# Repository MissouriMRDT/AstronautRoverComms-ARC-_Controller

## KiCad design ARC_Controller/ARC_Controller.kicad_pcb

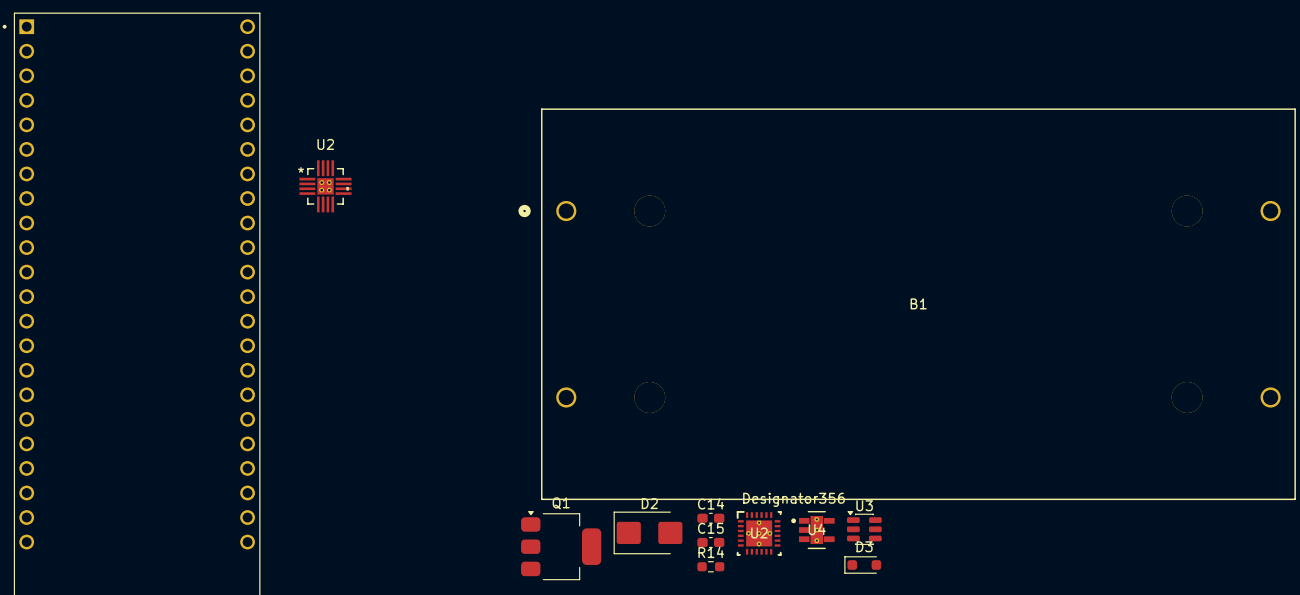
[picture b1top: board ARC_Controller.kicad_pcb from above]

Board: 2 copper layers, 12 parts (0 on the bottom side), 8 nets, no tracks yet.

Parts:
B1: BK-18650-PC4; BK-18650-PC4_MPD
C14: 0.1uF; C_0603_1608Metric_Pad1.08x0.95mm_HandSolder
C15: 10uF; C_0603_1608Metric_Pad1.08x0.95mm_HandSolder
D2: Z2SMBxxx; D_SMB
D3: 10V; D_SOD-323_HandSoldering
Q1: BS250; SOT-223
R14: 10k; R_0603_1608Metric_Pad0.98x0.95mm_HandSolder
U1: ESP32-S3-DEVKITC-1-N16R8V
U2: BQ25606RGER; BQ25606
U2#2: BQ24075RGTR; BQ24075_HandSolderable
U3: MT3608; SOT-23-6
U4: TLV75733PDYDR

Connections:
+3V3: U1.J1_1 (3V3), U1.J1_2 (3V3), U4.5 (OUT)
+12V: C14.1, C15.2, D3.1 (K), Q1.3 (S), U2.1 (VAC), U2.24 (VBUS)
+VSYS: U2.15 (SYS), U2.16 (SYS), U3.5 (IN), U4.1 (IN)
GND: B1.3, B1.4, C14.2, C15.1, D2.2 (A), R14.1, U1.J1_22 (GND), U1.J3_1 (GND), U1.J3_21 (GND), U1.J3_22 (GND), U2.6 (OTG), U2.9 (CE_N), U2.17 (GND), U2.18 (GND), U2.25 (PAD), U3.2 (GND), U4.2 (GND), U4.6 (Thermal_Pad)
unnamed: B1.1, B1.2, U2.13 (BAT), U2.14 (BAT)
unnamed: U2.19 (SW), U2.20 (SW)
unnamed: D2.1 (K), Q1.2 (D), Q1.4 (D)
unnamed: D3.2 (A), Q1.1 (G), R14.2
